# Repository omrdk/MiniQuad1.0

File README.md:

Drone Preview  

GUI Preview  

<table>
  <tr>
    <th>Type</th><th>Chipset</th>
  </tr>
  <tr>
    <td>MCU</td><td>CC2640@48MHz</td>
  </tr>
  <tr>
    <td>Accelerometer</td><td>MPU9250</td>
  </tr>
  <tr>
    <td>Gyro</td><td>MPU9250</td>
  </tr>
  <tr>
    <td>Barometer</td><td>BMP280</td>
  </tr>
</table>

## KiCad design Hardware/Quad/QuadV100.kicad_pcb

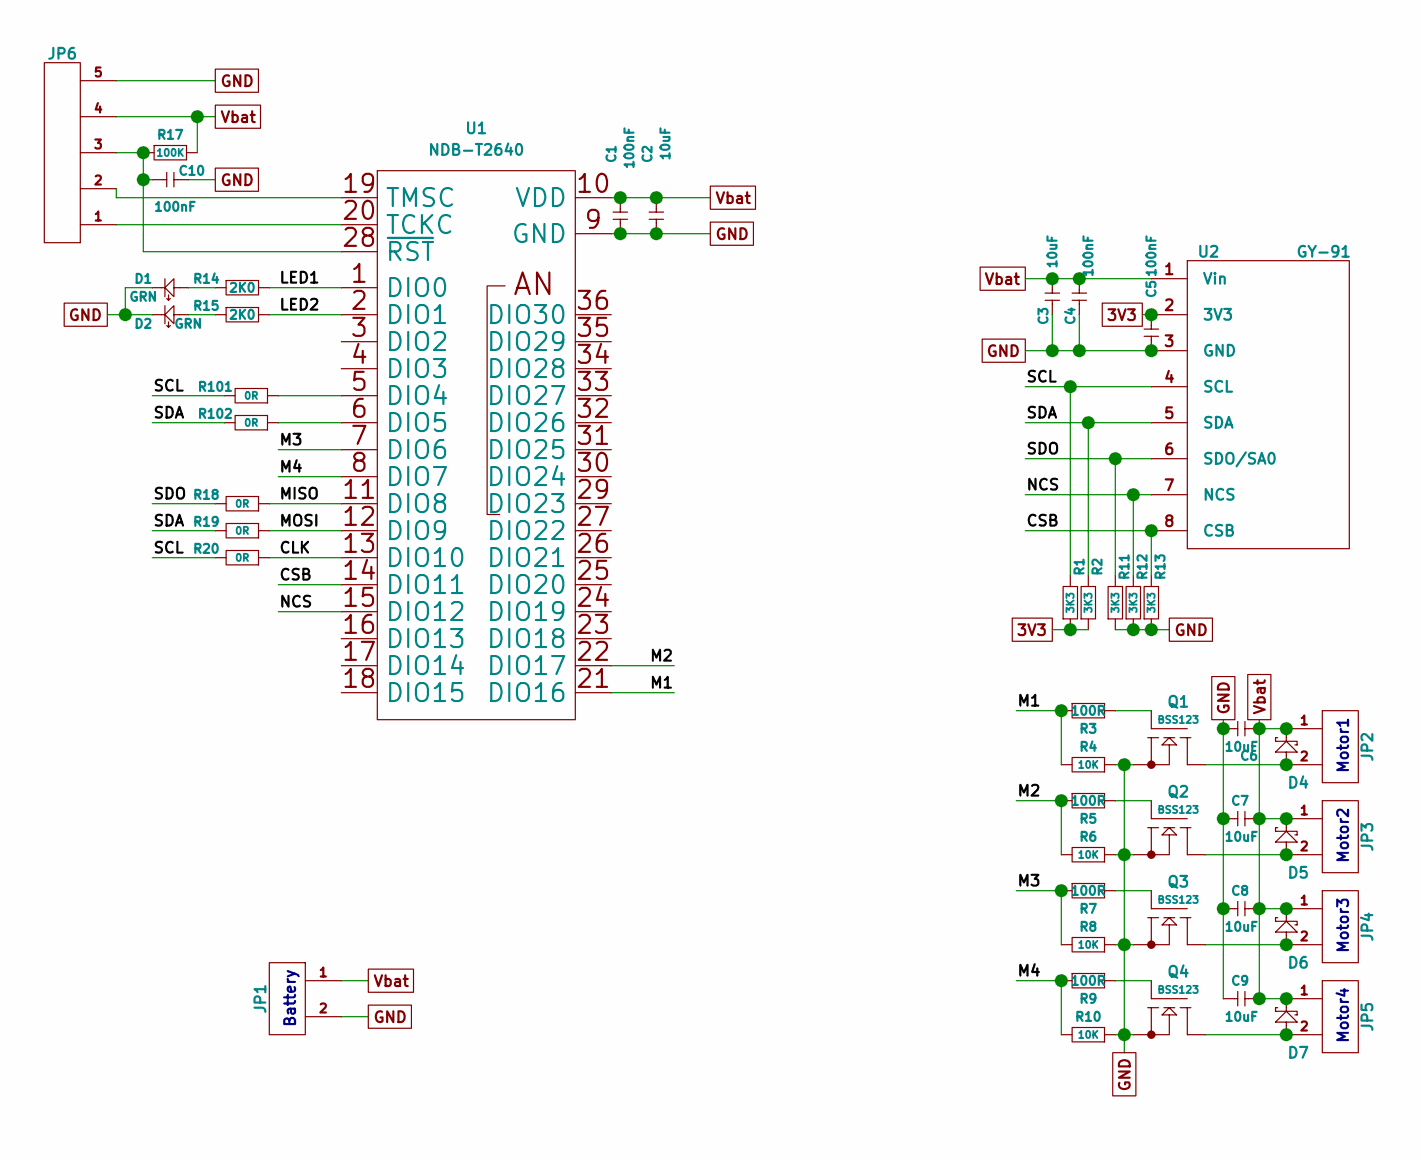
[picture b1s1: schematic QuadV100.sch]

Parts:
C1, C4, C5, C10: 100nF; SM0603_c
C2, C3, C6, C7, C8, C9: 10uF; SM0805_c
D1, D2: GRN; LED-0805
D4, D5, D6, D7: schottky; SOD123
JP1, JP2, JP3, JP4, JP5: CONN_02; Header_1x02_M_Vert_2.54_THT
JP6: CONN_05; Header_1x05_M_Vert_2.54_THT
Q1, Q2, Q3, Q4: BSS123; SOT23GDS
R1, R2, R11, R12, R13: 3K3; SM0603_r
R3, R5, R7, R9: 100R; SM0603_r
R4, R6, R8, R10: 10K; SM0603_r
R14, R15: 2K0; SM0603_r
R17: 100K; SM0603_r
R18, R19, R20, R101, R102: 0R; SM0603_r
U1: NDB-T2640; RF_Module_CC2640
U2: GY-91

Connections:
3V3: C5.2, R1.1, R2.1, U2.2 (3V3)
/CLK: R20.1, U1.13 (DIO10)
/CSB: R13.2, U1.14 (DIO11), U2.8 (CSB)
/LED1: R14.2, U1.1 (DIO0)
/LED2: R15.2, U1.2 (DIO1)
/M1: R3.1, R4.2, U1.21 (DIO16)
/M2: R5.1, R6.2, U1.22 (DIO17)
/M3: R7.1, R8.2, U1.7 (DIO6)
/M4: R9.1, R10.2, U1.8 (DIO7)
/MISO: R18.1, U1.11 (DIO8)
/MOSI: R19.1, U1.12 (DIO9)
/NCS: R12.2, U1.15 (DIO12), U2.7 (NCS)
/SCL: R1.2, R20.2, R101.2, U2.4 (SCL)
/SDA: R2.2, R19.2, R102.2, U2.5 (SDA)
/SDO: R11.2, R18.2, U2.6 (SDO/SA0)
GND: C1.1, C2.1, C3.1, C4.1, C5.1, C6.1, C7.1, C8.1, C9.1, C10.2, D1.2 (K), D2.2 (K), JP1.2, JP6.5, Q1.S, Q2.S, Q3.S, Q4.S, R4.1, R6.1, R8.1, R10.1, R11.1, R12.1, R13.1, U1.9 (GND), U2.3 (GND)
unnamed: C10.1, JP6.3, R17.1, U1.28 (~RST)
unnamed: D1.1 (A), R14.1
unnamed: D2.1 (A), R15.1
unnamed: D4.1 (A), JP2.2, Q1.D
unnamed: D5.1 (A), JP3.2, Q2.D
unnamed: D6.1 (A), JP4.2, Q3.D
unnamed: D7.1 (A), JP5.2, Q4.D
unnamed: JP6.1, U1.20 (TCKC)
unnamed: JP6.2, U1.19 (TMSC)
unnamed: Q1.G, R3.2
unnamed: Q2.G, R5.2
unnamed: Q3.G, R7.2
unnamed: Q4.G, R9.2
unnamed: R101.1, U1.5 (DIO4)
unnamed: R102.1, U1.6 (DIO5)
Vbat: C1.2, C2.2, C3.2, C4.2, C6.2, C7.2, C8.2, C9.2, D4.2 (K), D5.2 (K), D6.2 (K), D7.2 (K), JP1.1, JP2.1, JP3.1, JP4.1, JP5.1, JP6.4, R17.2, U1.10 (VDD), U2.1 (Vin)

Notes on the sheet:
Motor1
Motor2
Motor3
Motor4
Battery

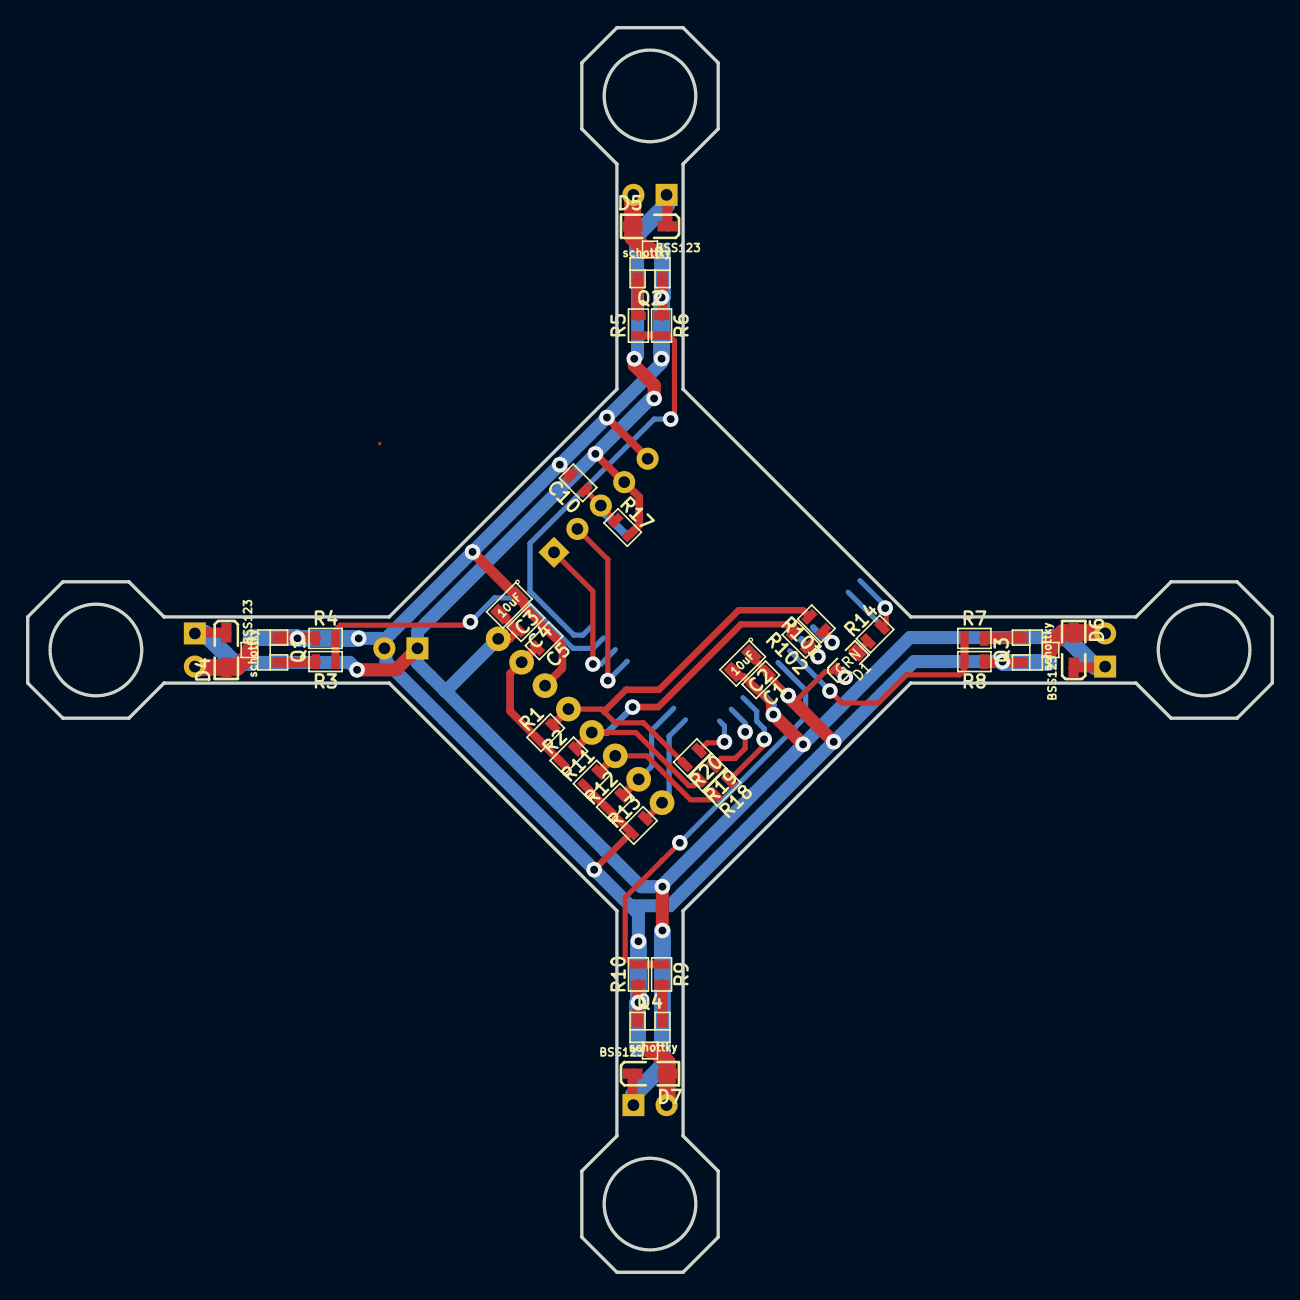
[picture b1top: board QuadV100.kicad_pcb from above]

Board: 4 copper layers, 95.5 x 95.5 mm, 49 parts (0 on the bottom side), 32 nets.

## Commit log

2021-03-10 gui overview added
2021-04-01 looptime updated @1KHz
